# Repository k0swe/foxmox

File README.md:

# FoxMox V2.6

A KiCad reproduction of Larry Benko **W0QE**'s _Low Power FoxMOX Controller
V2.6_ (December 2004), transcribed by Chris Keller **K0SWE**.

FoxMox is a PIC16F84A-based amateur-radio foxhunt/ARDF beacon controller. It
keys and modulates an Alinco DJ-S11 through the radio's 2.5 mm microphone jack,
is powered by the jack's microphone-bias supply, and uses two hexadecimal rotary
switches for field configuration.

This repository includes the reconstructed hardware, the original scanned
schematic, recovered and hardware-tested firmware, readable assembly source, and
field operating instructions.

## Repository contents

| Path                                                                     | Purpose                                                                                                |
| ------------------------------------------------------------------------ | ------------------------------------------------------------------------------------------------------ |
| [`USER-GUIDE.md`](USER-GUIDE.md)                                         | Full field switch settings, timing profiles, and staggered five-fox startup.                           |
| [`FoxMox-Quick-Reference.html`](FoxMox-Quick-Reference.html)             | Print-ready 4.25 × 5.5 inch front/back switch and deployment card.                                    |
| [`Hardware/README.md`](Hardware/README.md)                               | Circuit behavior, radio interface, power constraints, R5 service strap, and bench checks.              |
| [`Hardware/W0QE FoxMox scanned.pdf`](<Hardware/W0QE FoxMox scanned.pdf>) | Scan of the original W0QE schematic and source of truth for the hardware transcription.                |
| `Hardware/foxmox.kicad_sch` / `Hardware/foxmox.kicad_pcb`                | Reconstructed KiCad schematic and PCB.                                                                 |
| [`Hardware/foxmox.pdf`](Hardware/foxmox.pdf)                             | Exported reconstructed schematic.                                                                      |
| [`Firmware/README.md`](Firmware/README.md)                               | PIC programming, clock calibration, assembly builds, regression verification, and callsign generation. |
| `Firmware/foxmox-v2.6.hex`                                               | Original recovered, hardware-tested PIC programming image.                                             |
| `Firmware/foxmox-v2.6.asm`                                               | Validated, readable gpasm source that reproduces the recovered image exactly.                          |

## Quick start

- For field setup, begin with [`USER-GUIDE.md`](USER-GUIDE.md).
- For hardware construction or troubleshooting, see
  [`Hardware/README.md`](Hardware/README.md).
- For PIC programming or firmware builds, see
  [`Firmware/README.md`](Firmware/README.md).

The default assembly build identifies as **N0PUF** and is regression-tested
byte-for-byte against the recovered programming image.

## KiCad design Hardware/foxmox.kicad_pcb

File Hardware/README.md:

# FoxMox hardware

This directory contains the complete hardware design and its source references
for Larry Benko **W0QE**'s _Low Power FoxMOX Controller V2.6_ (December 2004),
transcribed by Chris Keller **K0SWE**.

| Path                            | Purpose                                                                           |
| ------------------------------- | --------------------------------------------------------------------------------- |
| `foxmox.kicad_pro`              | KiCad project entry point.                                                        |
| `foxmox.kicad_sch`              | Reconstructed schematic.                                                          |
| `foxmox.kicad_pcb`              | PCB layout.                                                                       |
| `foxmox.pdf`                    | PDF export of the reconstructed schematic.                                        |
| `W0QE FoxMox scanned.pdf`       | Scan of Larry Benko W0QE's original schematic; source of truth for transcription. |
| `fp-lib-table`, `sym-lib-table` | Project-local KiCad library tables.                                               |
| `Libraries/`                    | Project-local symbols, footprints, and 3D models.                                 |
| `Datasheets/`                   | Component datasheets.                                                             |

Open `foxmox.kicad_pro` from this directory. Library references use
`${KIPRJMOD}/Libraries/...`, so moving the project and `Libraries/` together
preserves their relative paths.

The target radio in this build is the **Alinco DJ-S11**, connected through its
2.5 mm microphone jack.

## How the controller keys the radio

The DJ-S11 microphone jack has ground, a bias rail, and audio, but no separate
PTT contact. The microphone tip serves as both the audio input and PTT sense.
The radio biases that contact to power an electret microphone and watches its DC
level: pulling it toward ground through a resistor keys the transmitter;
releasing it returns the radio to receive. Transmit audio is AC-coupled onto the
same contact.

This resistive keying arrangement is common on Alinco, Icom, and Yaesu handheld
microphone interfaces. It does not depend on a VOX setting in the radio; VOX
accessories for these radios implement their own resistive pull-down. Kenwood
accessory wiring is a notable exception because it commonly provides a separate
PTT contact.

### Audio path — PIC RA0, pin 17

```text
RA0 ── R1 20k ── R2 5k pot ──(wiper)── C4 1 µF ── P1 tip
                      └── bottom ── GND
```

RA0 generates the square-wave tone. R1 and R2 attenuate it, while C4 blocks DC
so the tone does not disturb the keying level.

W0QE annotated the original drawing:

> Adjust for 20 to 40 mV peak to peak. Or set R2 for ~300 ohms from wiper to
> ground.

That setting is internally consistent: `3.0 V × 300 / 25000 ≈ 36 mV`. Avoid
excessive drive; the source waveform is already square and harmonic-rich.

### PTT path — PIC RA1, pin 18

```text
RA1 ── R3 20k ── Q1 base (2N2222A, emitter → GND)
                 Q1 collector ── R4 2.7k ── P1 tip
```

RA1 high saturates Q1 and pulls the microphone tip toward ground through R4.
**R4, 2.7 kΩ, is the radio's keying resistor.** RA1 low turns Q1 off and allows
the microphone contact to return to its bias voltage.

Both paths meet at the microphone tip. In the PCB netlist, `Net-(C4-Pad2)`
contains `C4.2`, `P1.T`, and `R4.2`.

## Power source and current budget

The controller has no battery of its own. It is parasitically powered by the
radio's microphone-bias rail:

```text
P1 ring ── S3 (SPDT power switch) ── VDD ── U1.14, U1.4 (MCLR), C3, D1, TP1
P1 sleeve ── GND
```

W0QE recorded:

> Measured current draw @ 3.0 V from Ring to Sleeve = **0.5 mA idle, 0.9 mA
> transmitting**

This sub-milliamp supply is a binding design constraint. It explains the
PIC16F84, resistively attenuated square-wave audio, and absence of more
power-hungry circuitry. Before substituting another MCU, verify that its
complete idle and transmit current does not collapse the microphone-bias rail or
false-key the radio.

D1 is a 6.2 V zener used for overvoltage protection. It is not regulating the
normal approximately 3 V supply.

## R5 is the boot/service-mode strap

R5, 10 kΩ, is intentionally connected between **RA2 (PIC pin 1)** and **RA3 (PIC
pin 2)**. **RA4/T0CKI (PIC pin 3) is unconnected. Do not move R5 to RA4.**

The original scan is easy to misread:

1. The `R5 10k` text is printed below its resistor body, placing the label near
   the RA4 row even though the component itself connects RA2 to RA3. Component
   label placement in this drawing is not a reliable indication of connectivity.
2. The X on the RA4 row is a printed no-connect mark. The pin stub ends at that
   mark; it is not a wire crossed out by hand. Pixel measurements support that
   reading: its darkness matches printed material rather than the lighter pencil
   handwriting elsewhere on the scan.

   | Scan feature                     | Mean gray |
   | -------------------------------- | --------: |
   | Printed wire                     |        73 |
   | RA4 X mark                       |        81 |
   | Printed text                     |        89 |
   | Pencil handwriting at top margin |       140 |

The reconstructed schematic has an explicit RA4 no-connect at `(97.79, 105.41)`;
with U1 placed at `(80.01, 110.49)`, that location resolves to PIC pin 3. The
PCB independently names the pad `unconnected-(U1-TOCKI{slash}RA4-Pad3)`. The
reconstructed schematic and PCB therefore agree.

The firmware also proves R5's purpose: at reset RA3 is driven high while RA2 is
an input, so R5 pulls RA2 high for normal startup. Holding RA2 low during
startup enters the clock-calibration service mode; the firmware waits for RA2 to
be released before continuing. Moving R5 to RA4 would break that boot test.

The service-mode procedure is documented in
[`../Firmware/README.md`](../Firmware/README.md).

## Bench checks with an Alinco DJ-S11

Before relying on a rebuilt controller in the field, check it with the actual
radio and cable:

1. **Bias supply:** measure approximately 3 V from ring to sleeve and confirm it
   can source at least 1 mA without excessive sag.
2. **PTT keying:** confirm that the 2.7 kΩ pull-down keys reliably with both a
   fresh radio battery and a nearly discharged one. The microphone-bias voltage
   can move with battery condition.
3. **Audio level:** begin with R2 adjusted to approximately 300 Ω from wiper to
   ground, then verify 20–40 mV peak-to-peak or check deviation on a service
   monitor or trusted receiver.

## Verifying the transcription

The scanned schematic is lossy and its geometry is easy to misread. Use these
sources in descending order of confidence:

1. Treat `W0QE FoxMox scanned.pdf` as the source of truth for the original
   design.
2. Use the resolved nets in `foxmox.kicad_pcb` when checking the reconstructed
   connectivity. Footprint pad records carry their net names and avoid visual
   wire-tracing mistakes.
3. Cross-check hardware-dependent behavior against
   [`../Firmware/foxmox-v2.6.asm`](../Firmware/foxmox-v2.6.asm).
4. For close inspection of the scan, render it at high resolution:

   ```sh
   pdftoppm -r 300 -png "Hardware/W0QE FoxMox scanned.pdf" out
   ```

`Hardware/.history/` and `*.kicad_prl` are intentionally ignored by the outer
repository. They are local KiCad state, not versioned design artifacts.

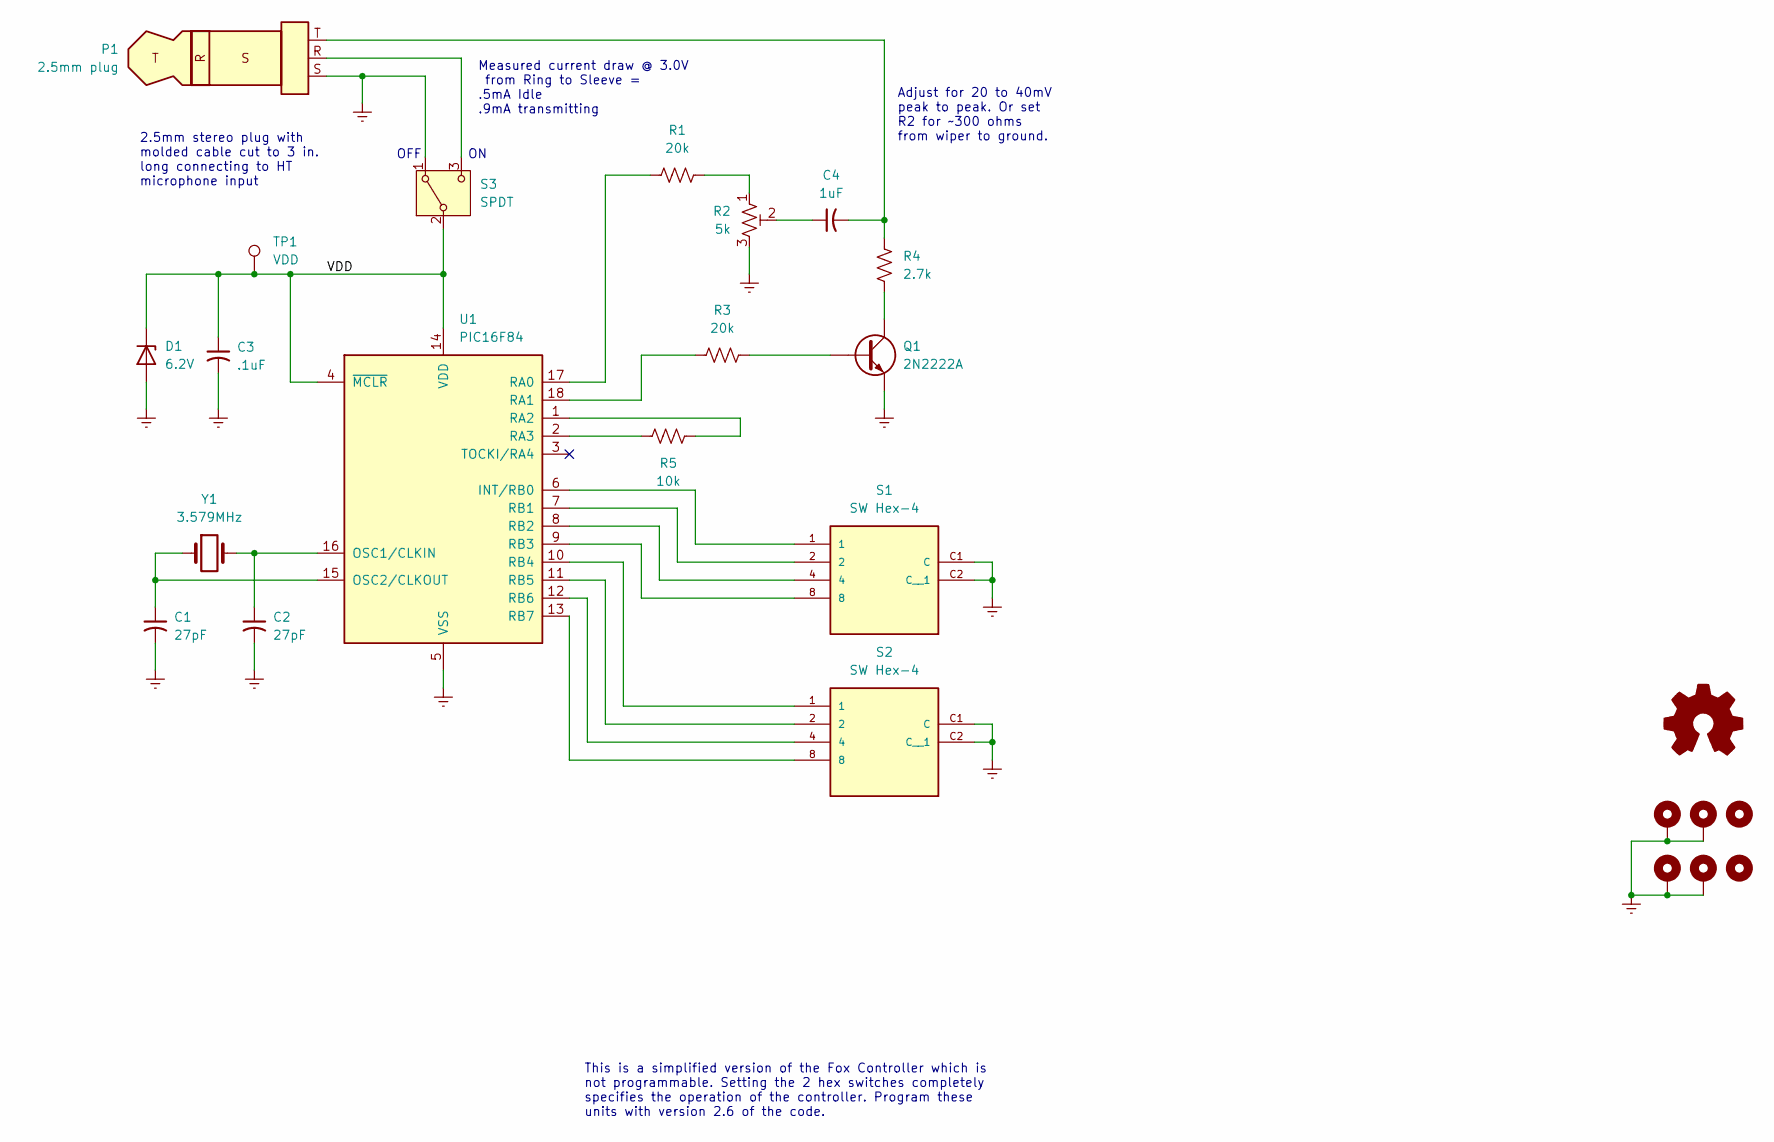
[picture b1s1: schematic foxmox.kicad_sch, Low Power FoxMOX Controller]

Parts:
C1, C2: 27pF; C_Disc_D4.3mm_W1.9mm_P5.00mm
C3: .1uF; C_Disc_D7.5mm_W5.0mm_P7.50mm
C4: 1uF; C_Disc_D7.5mm_W5.0mm_P7.50mm
D1: 6.2V; D_DO-35_SOD27_P7.62mm_Horizontal
H1, H2, H3, H4: MountingHole; MountingHole_2.5mm_Pad
H5, H6: MountingHole; MountingHole_2mm
P1: 2.5mm plug; TerminalBlock_Xinya_XY308-2.54-3P_1x03_P2.54mm_Horizontal
Q1: 2N2222A; TO-92_Inline_Wide
R1, R3: 20k; R_Axial_DIN0207_L6.3mm_D2.5mm_P15.24mm_Horizontal
R2: 5k; Potentiometer_Bourns_3266W_Vertical
R4: 2.7k; R_Axial_DIN0207_L6.3mm_D2.5mm_P15.24mm_Horizontal
R5: 10k; R_Axial_DIN0207_L6.3mm_D2.5mm_P15.24mm_Horizontal
S1, S2: SW Hex-4; SW_RDS5-16S-1065-D-67; PARTREV 1.0
S3: SPDT; SW_1218_EWI
SYM1: Logo_Open_Hardware_Small; OSHW-Logo2_7.3x6mm_SilkScreen
TP1: VDD; TestPoint_Pad_D2.0mm
U1: PIC16F84; CERDIP-18_W7.62mm_SideBrazed
Y1: 3.579MHz; Crystal_HC49-4H_Vertical

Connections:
/VDD: C3.1, D1.1 (K), S3.2 (B), TP1.1 (1_1), U1.4 (~MCLR), U1.14 (VDD)
GNDREF: C1.2, C2.2, C3.2, D1.2 (A), H1.1 (1_1), H2.1 (1_1), H3.1 (1_1), H4.1 (1_1), P1.S, Q1.1 (E), R2.3, S1.C1 (C), S1.C2 (C__1), S2.C1 (C), S2.C2 (C__1), S3.1 (A), U1.5 (VSS)
unnamed: C4.1, R2.2
unnamed: C4.2, P1.T, R4.2
unnamed: Q1.2 (B), R3.2
unnamed: Q1.3 (C), R4.1
unnamed: R1.2, R2.1
unnamed: P1.R, S3.3 (C)
unnamed: S1.1, U1.6 (INT/RB0)
unnamed: C2.1, U1.16 (OSC1/CLKIN), Y1.2
unnamed: C1.1, U1.15 (OSC2/CLKOUT), Y1.1
unnamed: R1.1, U1.17 (RA0)
unnamed: R3.1, U1.18 (RA1)
unnamed: R5.2, U1.1 (RA2)
unnamed: R5.1, U1.2 (RA3)
unnamed: S1.2, U1.7 (RB1)
unnamed: S1.4, U1.8 (RB2)
unnamed: S1.8, U1.9 (RB3)
unnamed: S2.1, U1.10 (RB4)
unnamed: S2.2, U1.11 (RB5)
unnamed: S2.4, U1.12 (RB6)
unnamed: S2.8, U1.13 (RB7)

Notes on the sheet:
OFF
Adjust for 20 to 40mV peak to peak. Or set R2 for ~300 ohms from wiper to ground.
This is a simplified version of the Fox Controller which is not programmable. Setting the 2 hex switches completely specifies the operation of the controller. Program these units with version 2.6 of the code.
Measured current draw @ 3.0V from Ring to Sleeve = .5mA Idle .9mA transmitting
2.5mm stereo plug with molded cable cut to 3 in. long connecting to HT microphone input

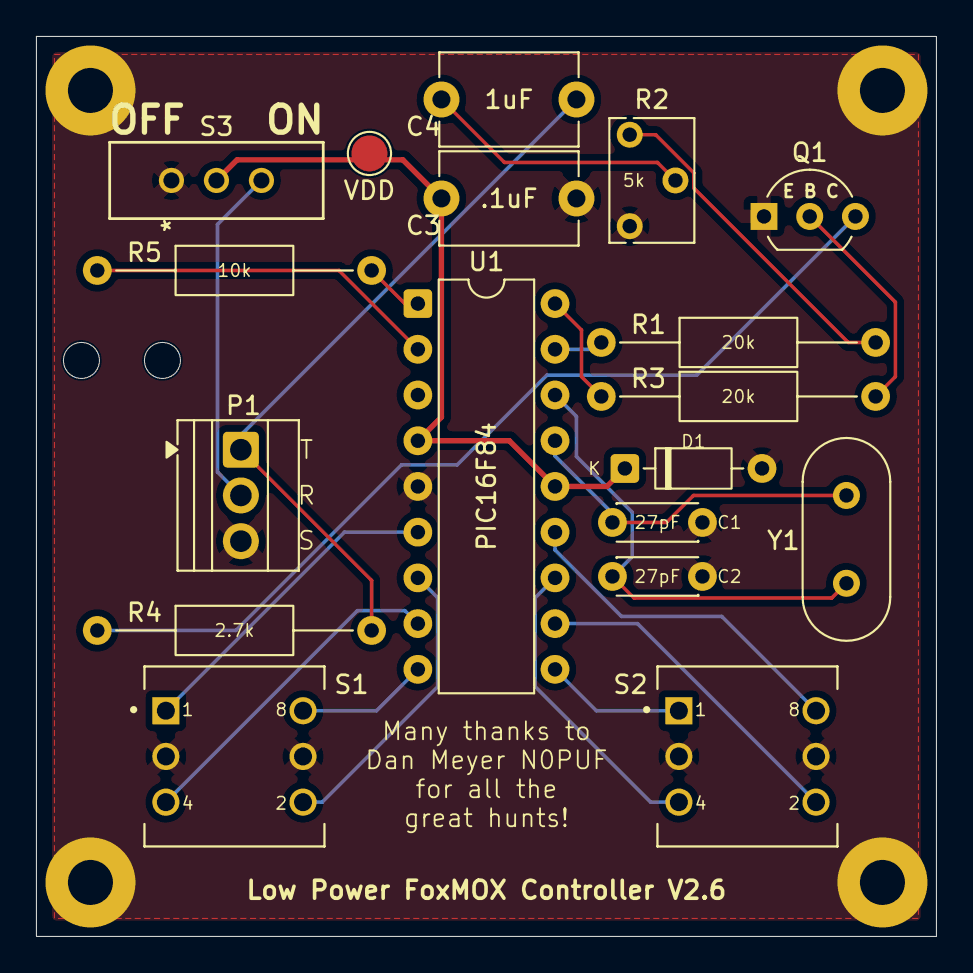
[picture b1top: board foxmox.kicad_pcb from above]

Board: 2 copper layers, 50.0 x 50.0 mm, 25 parts (1 on the bottom side), 22 nets.
